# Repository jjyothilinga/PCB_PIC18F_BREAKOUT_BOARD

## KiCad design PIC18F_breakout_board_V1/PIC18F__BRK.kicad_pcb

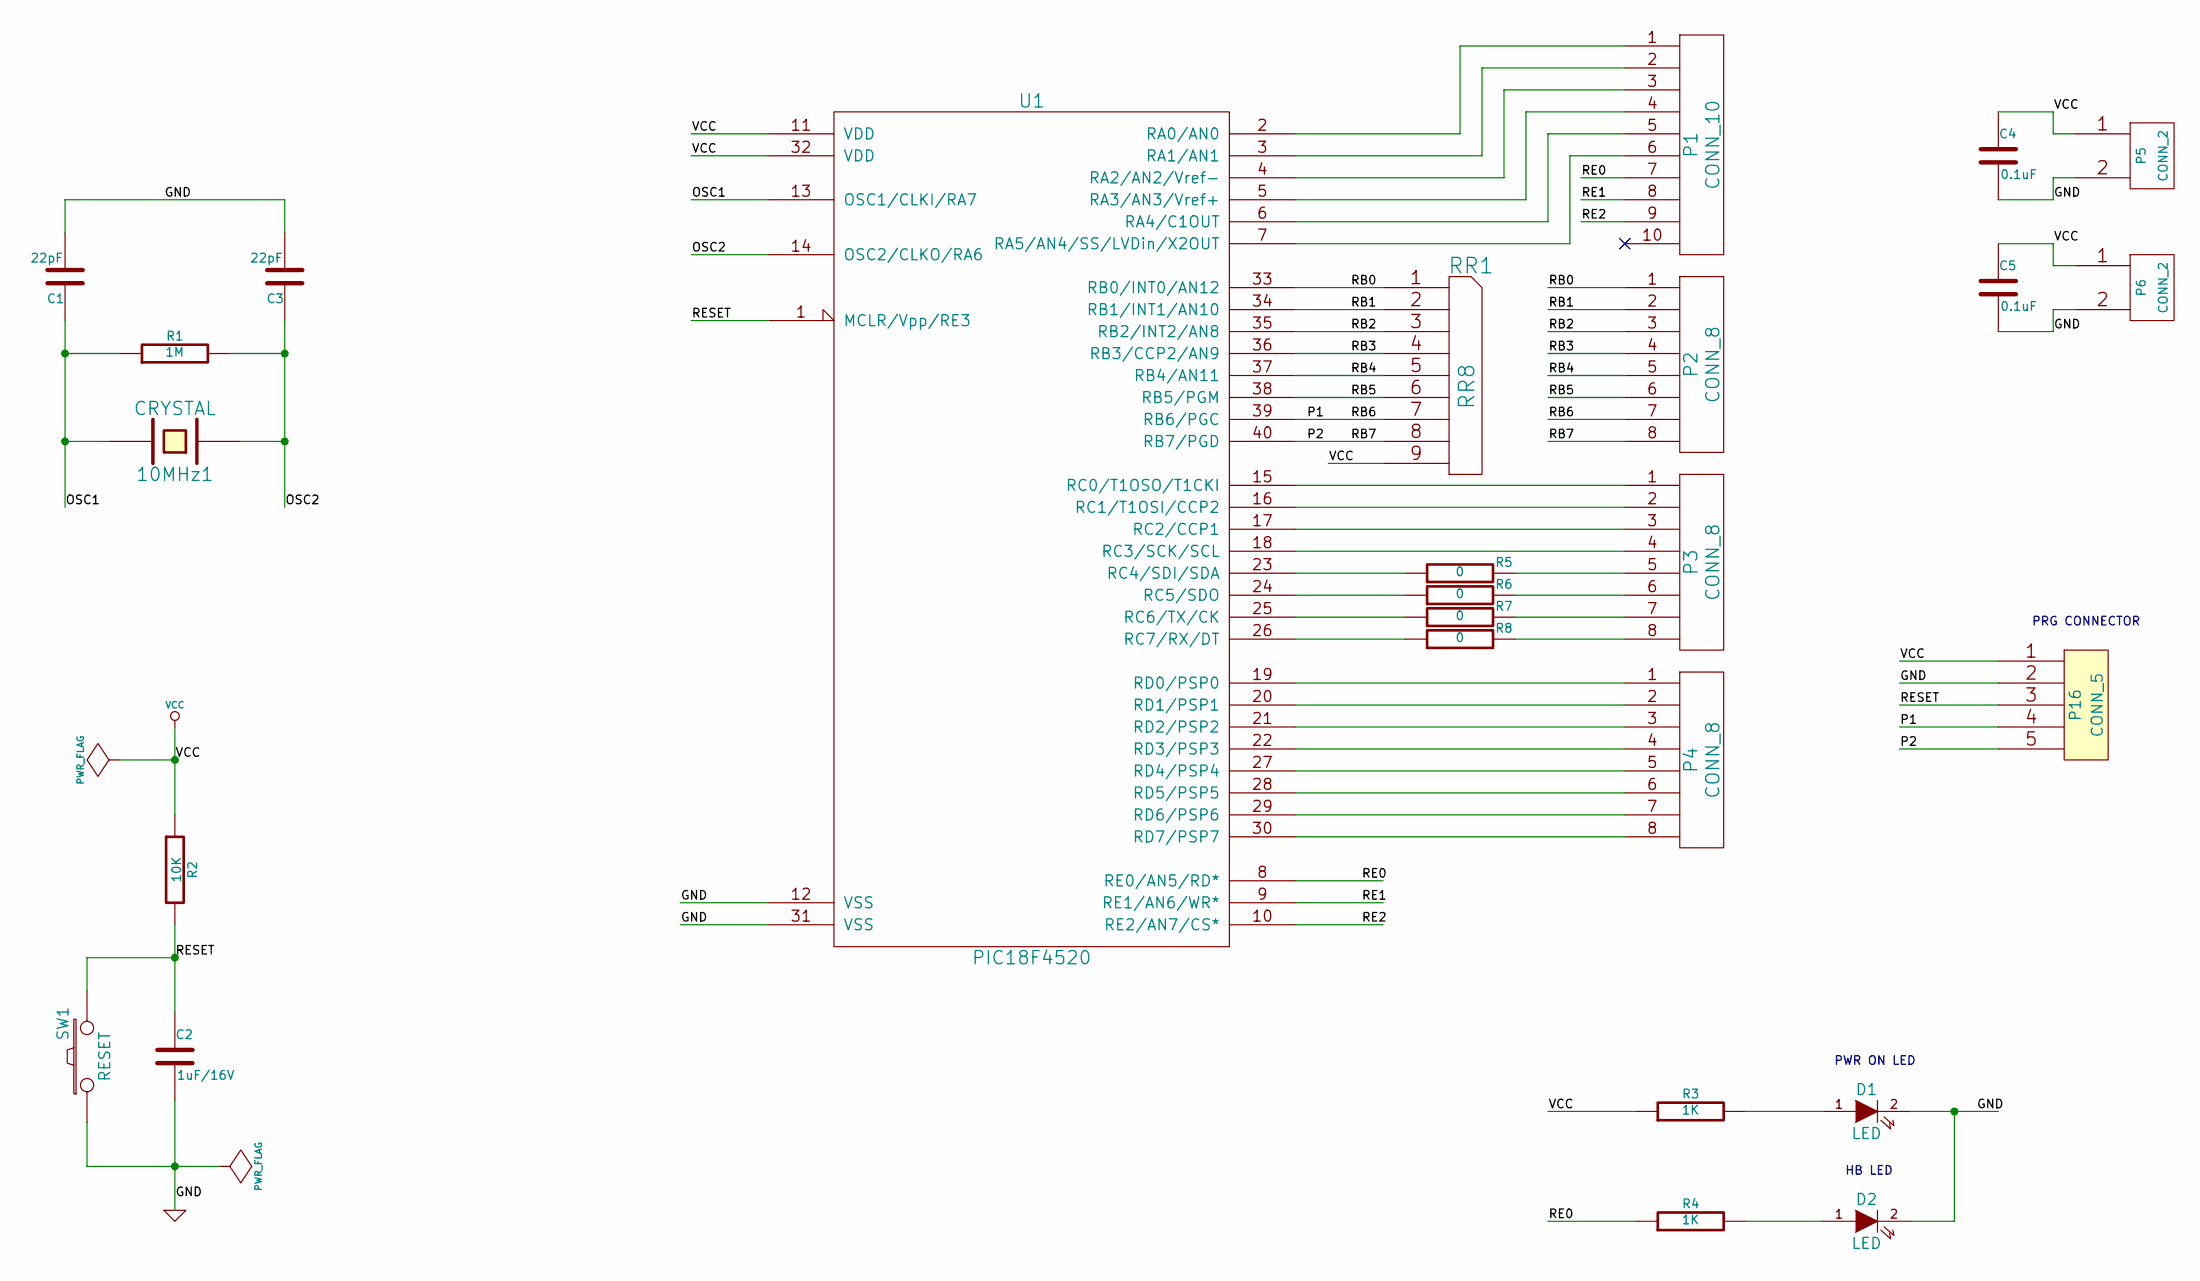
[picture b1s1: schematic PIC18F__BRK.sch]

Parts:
10MHz1: CRYSTAL
C1, C3: 22pF
C2: 1uF/16V
C4, C5: 0.1uF
D1, D2: LED
P1: CONN_10
P2, P3, P4: CONN_8
P5, P6: CONN_2
P16: CONN_5
R1: 1M
R2: 10K
R3, R4: 1K
R5, R6, R7, R8: 0
RR1: RR8
SW1: RESET
U1: PIC18F4520

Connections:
/OSC1: 10MHz1.2, C1.1, R1.1, U1.13 (OSC1/CLKI/RA7)
/OSC2: 10MHz1.1, C3.1, R1.2, U1.14 (OSC2/CLKO/RA6)
/P1: P2.7, P16.4, RR1.7, U1.39 (RB6/PGC)
/P2: P2.8, P16.5, RR1.8, U1.40 (RB7/PGD)
/RB0: P2.1, RR1.1 (COM), U1.33 (RB0/INT0/AN12)
/RB1: P2.2, RR1.2, U1.34 (RB1/INT1/AN10)
/RB2: P2.3, RR1.3, U1.35 (RB2/INT2/AN8)
/RB3: P2.4, RR1.4, U1.36 (RB3/CCP2/AN9)
/RB4: P2.5, RR1.5, U1.37 (RB4/AN11)
/RB5: P2.6, RR1.6, U1.38 (RB5/PGM)
/RE0: P1.7, R4.1, U1.8 (RE0/AN5/RD*)
/RE1: P1.8, U1.9 (RE1/AN6/WR*)
/RE2: P1.9, U1.10 (RE2/AN7/CS*)
/RESET: C2.1, P16.3, R2.2, SW1.2, U1.1 (MCLR/Vpp/RE3)
GND: C1.2, C2.2, C3.2, C4.2, C5.2, D1.2 (K), D2.2 (K), P5.2 (PM), P6.2 (PM), P16.2, SW1.1, U1.12 (VSS), U1.31 (VSS)
unnamed: P3.2, U1.16 (RC1/T1OSI/CCP2)
unnamed: P4.7, U1.29 (RD6/PSP6)
unnamed: P4.6, U1.28 (RD5/PSP5)
unnamed: P4.5, U1.27 (RD4/PSP4)
unnamed: P4.4, U1.22 (RD3/PSP3)
unnamed: P4.3, U1.21 (RD2/PSP2)
unnamed: P4.2, U1.20 (RD1/PSP1)
unnamed: P4.1, U1.19 (RD0/PSP0)
unnamed: P3.4, U1.18 (RC3/SCK/SCL)
unnamed: P3.3, U1.17 (RC2/CCP1)
unnamed: P4.8, U1.30 (RD7/PSP7)
unnamed: P3.1, U1.15 (RC0/T1OSO/T1CKI)
unnamed: P1.1, U1.2 (RA0/AN0)
unnamed: P1.2, U1.3 (RA1/AN1)
unnamed: P1.3, U1.4 (RA2/AN2/Vref-)
unnamed: P1.6, U1.7 (RA5/AN4/SS/LVDin/X2OUT)
unnamed: P1.4, U1.5 (RA3/AN3/Vref+)
unnamed: P1.5, U1.6 (RA4/C1OUT)
unnamed: R8.1, U1.26 (RC7/RX/DT)
unnamed: R6.1, U1.24 (RC5/SDO)
unnamed: R7.1, U1.25 (RC6/TX/CK)
unnamed: P3.8, R8.2
unnamed: P3.7, R7.2
unnamed: P3.6, R6.2
unnamed: P3.5, R5.2
unnamed: R5.1, U1.23 (RC4/SDI/SDA)
unnamed: D2.1 (A), R4.2
unnamed: D1.1 (A), R3.2
VCC: C4.1, C5.1, P5.1, P6.1, P16.1, R2.1, R3.1, RR1.9, U1.11 (VDD), U1.32 (VDD)

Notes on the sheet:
HB LED
PWR ON LED
PRG CONNECTOR

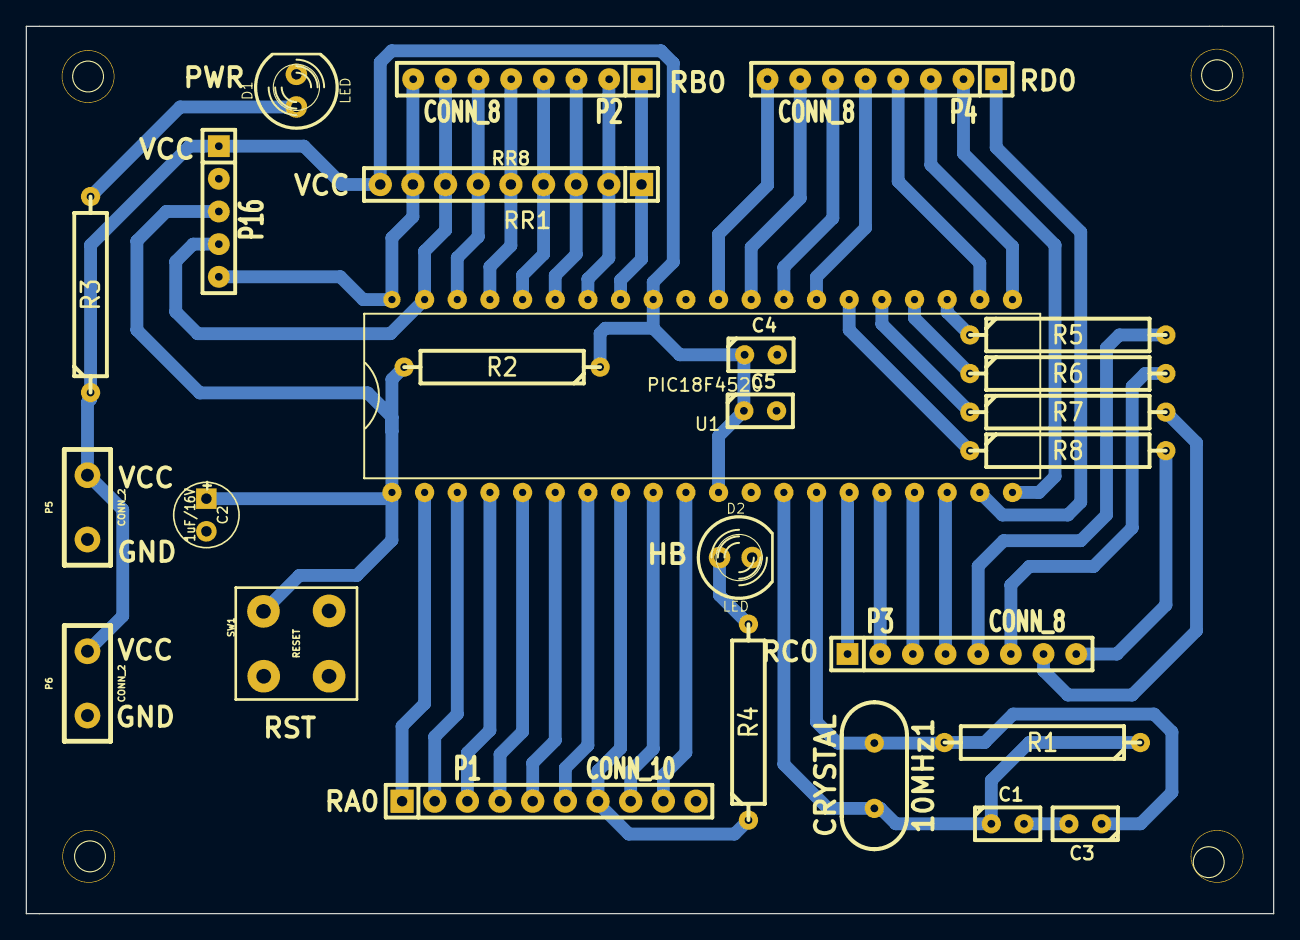
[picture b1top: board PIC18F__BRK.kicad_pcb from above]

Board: 2 copper layers, 97.0 x 69.0 mm, 26 parts (0 on the bottom side), 44 nets.

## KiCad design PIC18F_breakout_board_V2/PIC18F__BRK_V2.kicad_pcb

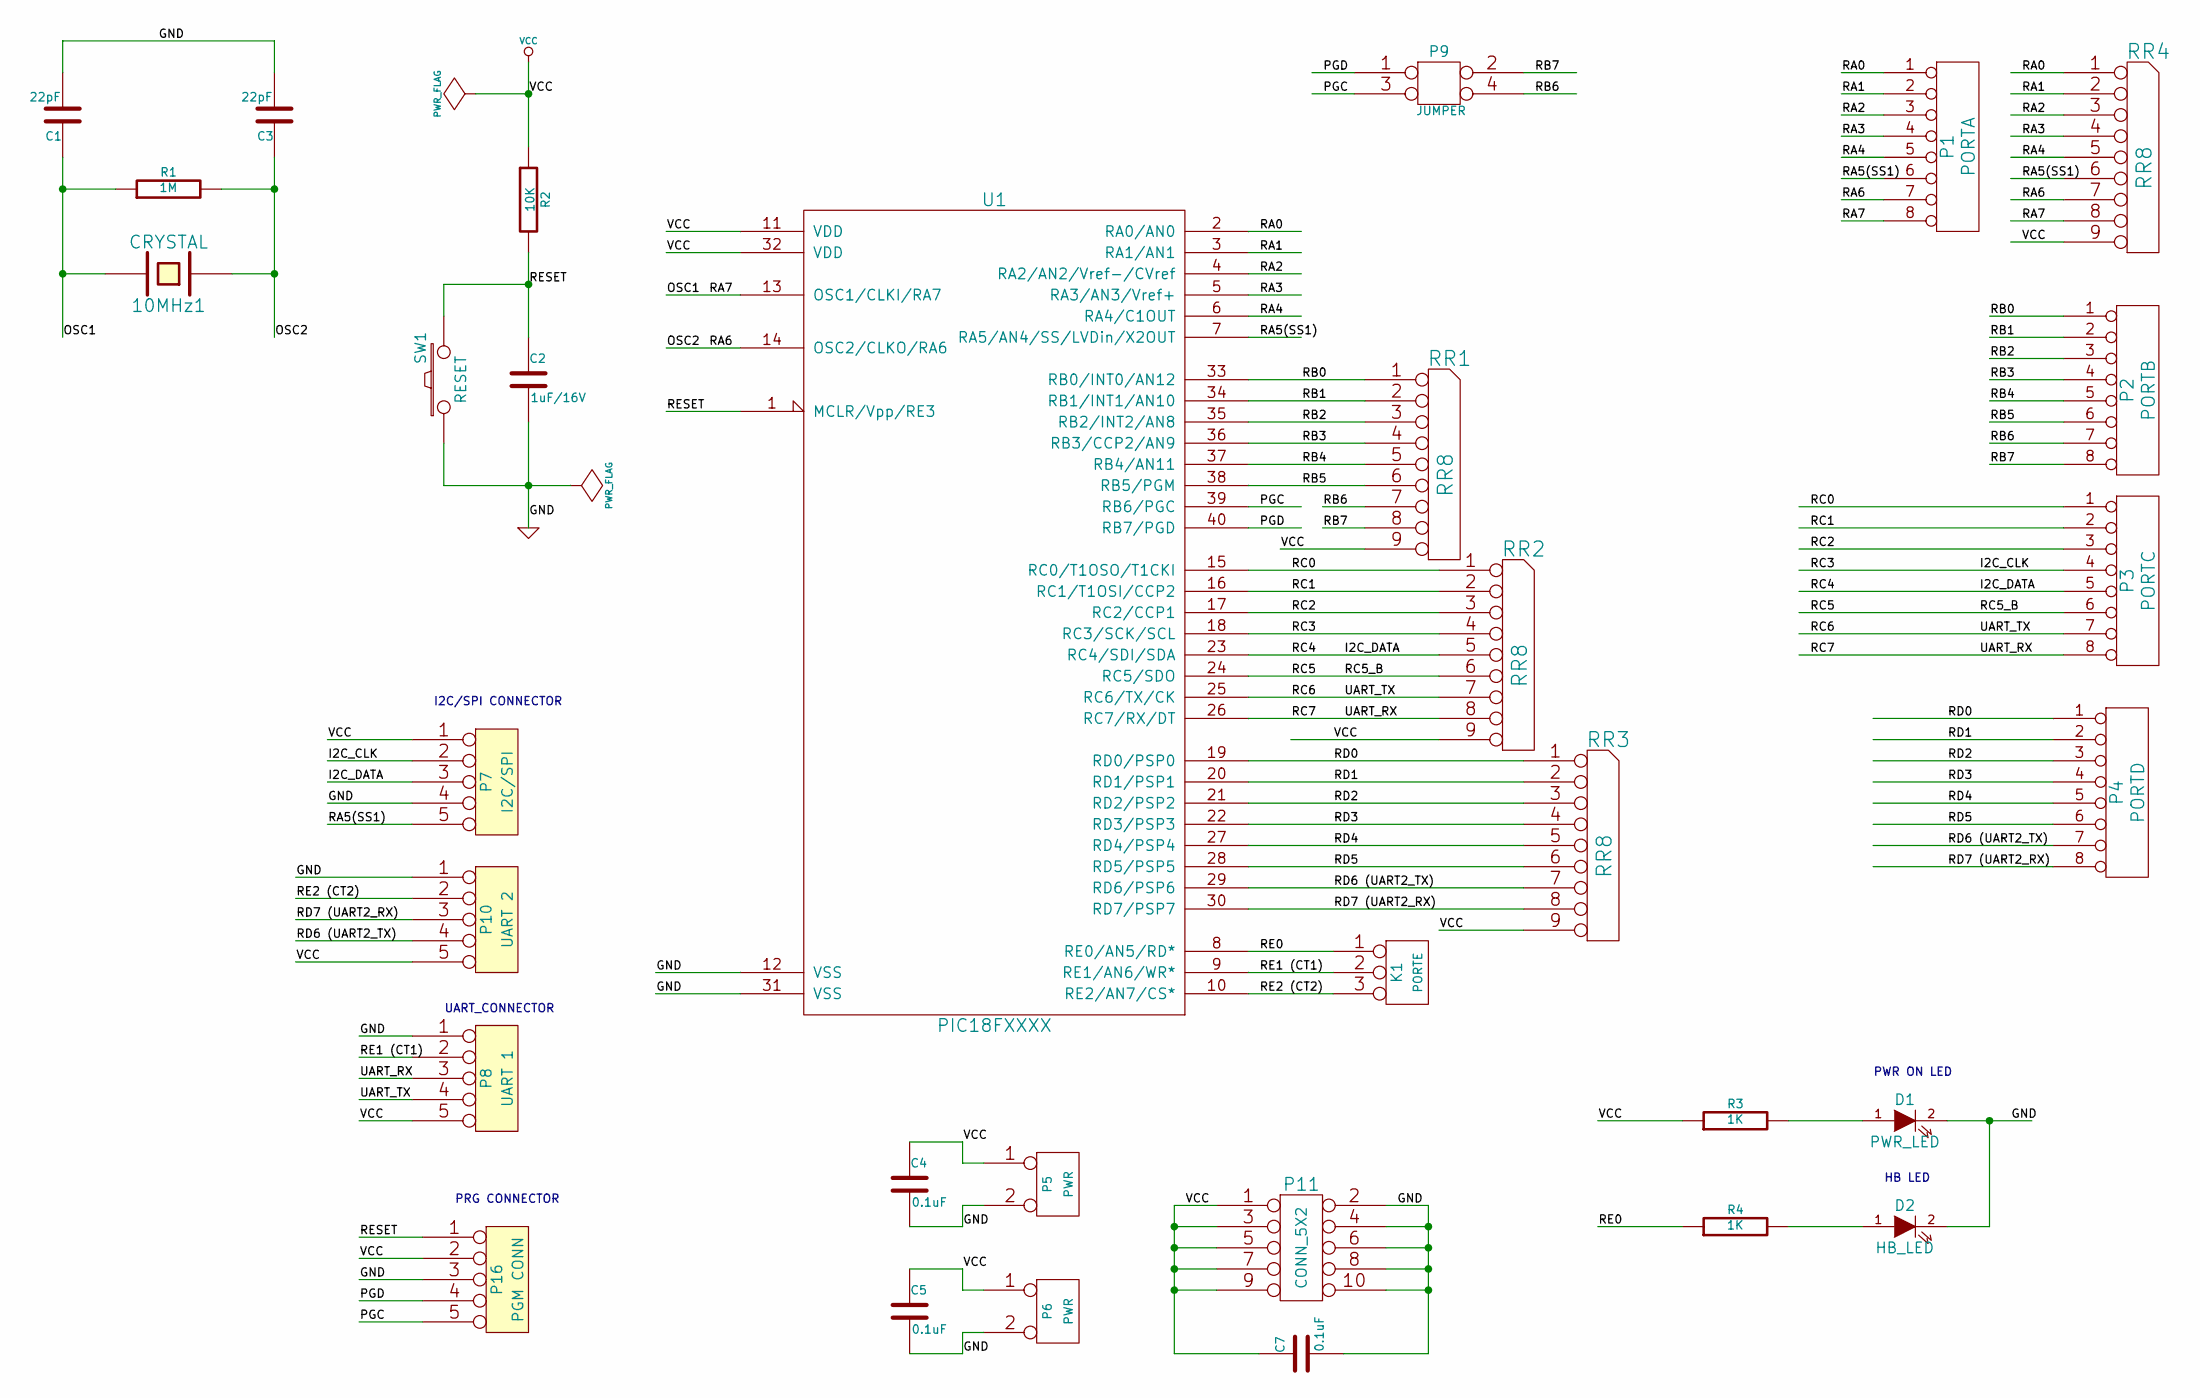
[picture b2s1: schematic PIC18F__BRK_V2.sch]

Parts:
10MHz1: CRYSTAL
C1, C3: 22pF
C2: 1uF/16V
C4, C5, C7: 0.1uF
D1: PWR_LED
D2: HB_LED
K1: PORTE
P1: PORTA
P2: PORTB
P3: PORTC
P4: PORTD
P5, P6: PWR
P7: I2C/SPI
P8: UART 1
P9: JUMPER
P10: UART 2
P11: CONN_5X2
P16: PGM CONN
R1: 1M
R2: 10K
R3, R4: 1K
RR1, RR2, RR3, RR4: RR8
SW1: RESET
U1: PIC18FXXXX

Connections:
/I2C_CLK: P3.4, P7.2, RR2.4, U1.18 (RC3/SCK/SCL)
/I2C_DATA: P3.5, P7.3, RR2.5, U1.23 (RC4/SDI/SDA)
/OSC1: 10MHz1.2, C1.1, P1.8, R1.1, RR4.8, U1.13 (OSC1/CLKI/RA7)
/OSC2: 10MHz1.1, C3.1, P1.7, R1.2, RR4.7, U1.14 (OSC2/CLKO/RA6)
/PGC: P9.3, P16.5, U1.39 (RB6/PGC)
/PGD: P9.1, P16.4, U1.40 (RB7/PGD)
/RA0: P1.1, RR4.1 (COM), U1.2 (RA0/AN0)
/RA1: P1.2, RR4.2, U1.3 (RA1/AN1)
/RA2: P1.3, RR4.3, U1.4 (RA2/AN2/Vref-/CVref)
/RA3: P1.4, RR4.4, U1.5 (RA3/AN3/Vref+)
/RA4: P1.5, RR4.5, U1.6 (RA4/C1OUT)
/RA5(SS1): P1.6, P7.5, RR4.6, U1.7 (RA5/AN4/SS/LVDin/X2OUT)
/RB0: P2.1, RR1.1 (COM), U1.33 (RB0/INT0/AN12)
/RB1: P2.2, RR1.2, U1.34 (RB1/INT1/AN10)
/RB2: P2.3, RR1.3, U1.35 (RB2/INT2/AN8)
/RB3: P2.4, RR1.4, U1.36 (RB3/CCP2/AN9)
/RB4: P2.5, RR1.5, U1.37 (RB4/AN11)
/RB5: P2.6, RR1.6, U1.38 (RB5/PGM)
/RB6: P2.7, P9.4, RR1.7
/RB7: P2.8, P9.2, RR1.8
/RC0: P3.1, RR2.1 (COM), U1.15 (RC0/T1OSO/T1CKI)
/RC1: P3.2, RR2.2, U1.16 (RC1/T1OSI/CCP2)
/RC2: P3.3, RR2.3, U1.17 (RC2/CCP1)
/RC5: P3.6, RR2.6, U1.24 (RC5/SDO)
/RC6: P3.7, P8.4, RR2.7, U1.25 (RC6/TX/CK)
/RC7: P3.8, P8.3, RR2.8, U1.26 (RC7/RX/DT)
/RD0: P4.1, RR3.1 (COM), U1.19 (RD0/PSP0)
/RD1: P4.2, RR3.2, U1.20 (RD1/PSP1)
/RD2: P4.3, RR3.3, U1.21 (RD2/PSP2)
/RD3: P4.4, RR3.4, U1.22 (RD3/PSP3)
/RD4: P4.5, RR3.5, U1.27 (RD4/PSP4)
/RD5: P4.6, RR3.6, U1.28 (RD5/PSP5)
/RD6 (UART2_TX): P4.7, P10.4, RR3.7, U1.29 (RD6/PSP6)
/RD7 (UART2_RX): P4.8, P10.3, RR3.8, U1.30 (RD7/PSP7)
/RE0: K1.1, R4.1, U1.8 (RE0/AN5/RD*)
/RE1 (CT1): K1.2 (PM), P8.2, U1.9 (RE1/AN6/WR*)
/RE2 (CT2): K1.3, P10.2, U1.10 (RE2/AN7/CS*)
/RESET: C2.1, P16.1, R2.2, SW1.2, U1.1 (MCLR/Vpp/RE3)
GND: C1.2, C2.2, C3.2, C4.2, C5.2, C7.2, D1.2 (K), D2.2 (K), P5.2 (PM), P6.2 (PM), P7.4, P8.1, P10.1, P11.2, P11.4, P11.6, P11.8, P11.10, P16.3, SW1.1, U1.12 (VSS), U1.31 (VSS)
unnamed: D1.1 (A), R3.2
unnamed: D2.1 (A), R4.2
VCC: C4.1, C5.1, C7.1, P5.1, P6.1, P7.1, P8.5, P10.5, P11.1, P11.3, P11.5, P11.7, P11.9, P16.2, R2.1, R3.1, RR1.9, RR2.9, RR3.9, RR4.9, U1.11 (VDD), U1.32 (VDD)

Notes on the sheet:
HB LED
PWR ON LED
PRG CONNECTOR
UART_CONNECTOR
I2C/SPI CONNECTOR

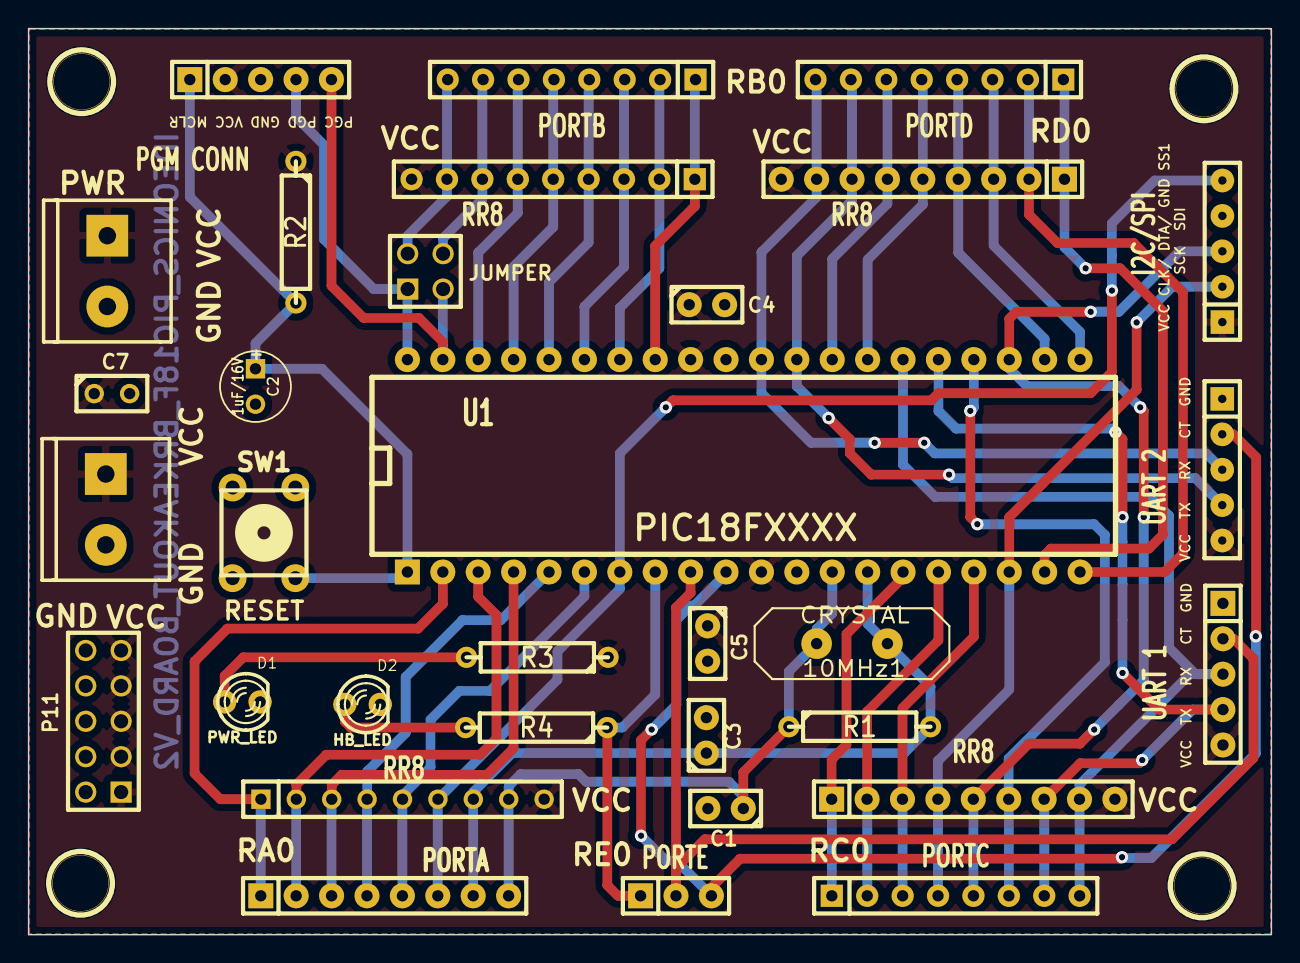
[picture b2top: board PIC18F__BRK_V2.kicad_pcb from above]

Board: 2 copper layers, 89.2 x 65.0 mm, 36 parts (0 on the bottom side), 42 nets.

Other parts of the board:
1PIN, 1PIN#2, 1PIN#3, 1PIN#4: P***; 1pin

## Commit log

2015-05-30 :neckbeard: Added .gitattributes & .gitignore files
2015-05-30 Project creation
